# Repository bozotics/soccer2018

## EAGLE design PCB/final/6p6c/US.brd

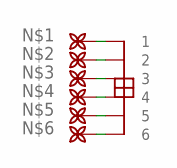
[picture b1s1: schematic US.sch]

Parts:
C1: 6P6C_FEMALESMD; 6P6C_FEMALE
PAD1, PAD2, PAD3, PAD4, PAD5, PAD6: BETTERPAD_2.54; SUPERIORSIM

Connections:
unnamed: C1.1, PAD1..
unnamed: C1.2, PAD2..
unnamed: C1.3, PAD3..
unnamed: C1.4, PAD4..
unnamed: C1.5, PAD5..
unnamed: C1.6, PAD6..

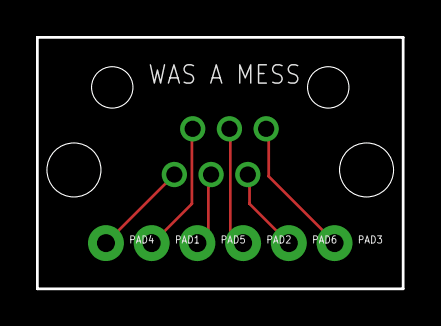
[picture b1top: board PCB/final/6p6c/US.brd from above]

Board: 2 copper layers, 20.3 x 14.0 mm, 7 parts (0 on the bottom side), 6 nets.

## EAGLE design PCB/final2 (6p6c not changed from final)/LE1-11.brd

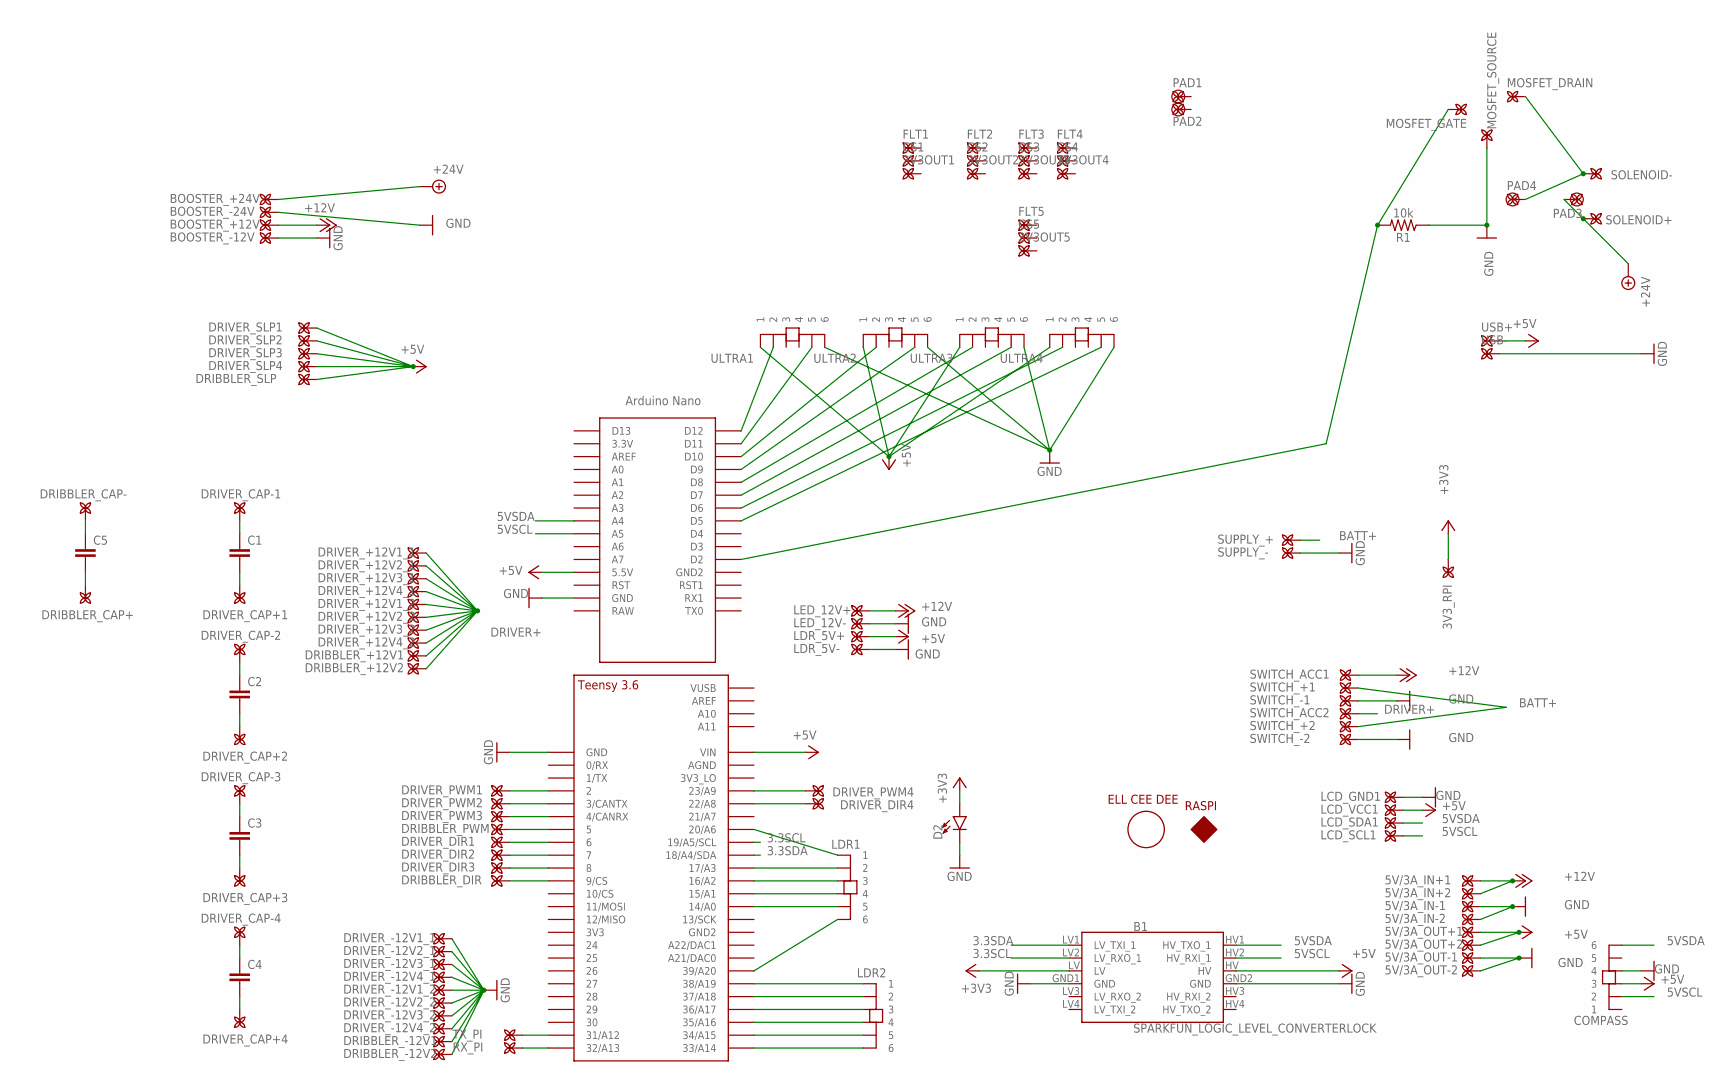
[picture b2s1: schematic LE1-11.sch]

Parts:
3V3OUT1, 3V3OUT2, 3V3OUT3, 3V3OUT4, 3V3OUT5, 3V3_RPI, 5V/3A_IN+1, 5V/3A_IN+2, 5V/3A_IN-1, 5V/3A_IN-2, 5V/3A_OUT+1, 5V/3A_OUT+2, 5V/3A_OUT-1, 5V/3A_OUT-2: BETTERPAD_2.54; SUPERIORSIM
B1: SPARKFUN_LOGIC_LEVEL_CONVERTERLOCK; SPARKFUN_LOGIC_LEVEL_CONVERTER_LOCK
BOOSTER_+12V, BOOSTER_+24V: BETTERPAD_2.54; SUPERIORSIM
BOOSTER_-12V, BOOSTER_-24V: BETTERPAD_2.54; SUPERIORSIM
C1, C2, C3, C4, C5: C5/7.2; C5B7.2
COMPASS: 6P6C_FEMALESMD; 6P6C_FEMALE
CS1, CS2, CS3, CS4, CS5: BETTERPAD_2.54; SUPERIORSIM
D2: LED-3MM-NO_SILK; LED_3MM-NS
DRIBBLER_+12V1, DRIBBLER_+12V2: BETTERPAD_2.54; SUPERIORSIM
DRIBBLER_-12V1, DRIBBLER_-12V2: BETTERPAD_2.54; SUPERIORSIM
DRIBBLER_CAP+: BETTERPAD_2.54; SUPERIORSIM
DRIBBLER_CAP-: BETTERPAD_2.54; SUPERIORSIM
DRIBBLER_DIR: BETTERPAD_2.54; SUPERIORSIM
DRIBBLER_PWM: BETTERPAD_2.54; SUPERIORSIM
DRIBBLER_SLP: BETTERPAD_2.54; SUPERIORSIM
DRIVER_+12V1_1, DRIVER_+12V1_2, DRIVER_+12V2_1, DRIVER_+12V2_2, DRIVER_+12V3_1, DRIVER_+12V3_2, DRIVER_+12V4_1, DRIVER_+12V4_2: BETTERPAD_2.54; SUPERIORSIM
DRIVER_-12V1_1, DRIVER_-12V1_2, DRIVER_-12V2_1, DRIVER_-12V2_2, DRIVER_-12V3_1, DRIVER_-12V3_2, DRIVER_-12V4_1, DRIVER_-12V4_2: BETTERPAD_2.54; SUPERIORSIM
DRIVER_CAP+1, DRIVER_CAP+2, DRIVER_CAP+3, DRIVER_CAP+4: BETTERPAD_2.54; SUPERIORSIM
DRIVER_CAP-1, DRIVER_CAP-2, DRIVER_CAP-3, DRIVER_CAP-4: BETTERPAD_2.54; SUPERIORSIM
DRIVER_DIR1, DRIVER_DIR2, DRIVER_DIR3, DRIVER_DIR4: BETTERPAD_2.54; SUPERIORSIM
DRIVER_PWM1, DRIVER_PWM2, DRIVER_PWM3, DRIVER_PWM4: BETTERPAD_2.54; SUPERIORSIM
DRIVER_SLP1, DRIVER_SLP2, DRIVER_SLP3, DRIVER_SLP4: BETTERPAD_2.54; SUPERIORSIM
FLT1, FLT2, FLT3, FLT4, FLT5: BETTERPAD_2.54; SUPERIORSIM
LCD1: LCD-16X2SILK; LCD-16X2
LCD_GND1: BETTERPAD_2.54; SUPERIORSIM
LCD_SCL1: BETTERPAD_2.54; SUPERIORSIM
LCD_SDA1: BETTERPAD_2.54; SUPERIORSIM
LCD_VCC1: BETTERPAD_2.54; SUPERIORSIM
LDR1, LDR2: 6P6C_FEMALESMD; 6P6C_FEMALE
LDR_5V+, LDR_5V-: BETTERPAD_2.54; SUPERIORSIM
LED_12V+, LED_12V-: BETTERPAD_2.54; SUPERIORSIM
MOSFET_DRAIN: BETTERPAD_2.54; SUPERIORSIM
MOSFET_GATE: BETTERPAD_2.54; SUPERIORSIM
MOSFET_SOURCE: BETTERPAD_2.54; SUPERIORSIM
PAD1, PAD2, PAD3, PAD4: BETTERPAD_2.54/1.5; 1,5
PCB1: RPI3
R1: 10k; AXIAL-0.3
RX_PI: BETTERPAD_2.54; SUPERIORSIM
SOLENOID+: BETTERPAD_2.54; SUPERIORSIM
SOLENOID-: BETTERPAD_2.54; SUPERIORSIM
SUPPLY_+: BETTERPAD_2.54; SUPERIORSIM
SUPPLY_-: BETTERPAD_2.54; SUPERIORSIM
SWITCH_+1, SWITCH_+2: BETTERPAD_2.54; SUPERIORSIM
SWITCH_-1, SWITCH_-2: BETTERPAD_2.54; SUPERIORSIM
SWITCH_ACC1, SWITCH_ACC2: BETTERPAD_2.54; SUPERIORSIM
TX_PI: BETTERPAD_2.54; SUPERIORSIM
U$1: TEENSY_3.5/3.6_BASIC
U$2: NANO
ULTRA1, ULTRA2, ULTRA3, ULTRA4: 6P6C_FEMALESMD; 6P6C_FEMALE
USB+: BETTERPAD_2.54; SUPERIORSIM
USB-: BETTERPAD_2.54; SUPERIORSIM

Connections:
3.3SCL: B1.LV2 (LV_RXO_1), U$1.19/A5/SCL
3.3SDA: B1.LV1 (LV_TXI_1), U$1.18/A4/SDA
5VSCL: B1.HV2 (HV_RXI_1), COMPASS.2, LCD_SCL1.., U$2.A5
5VSDA: B1.HV1 (HV_TXO_1), COMPASS.6, LCD_SDA1.., U$2.A4
+3V3: 3V3_RPI.., B1.LV, D2.A
+5V: 5V/3A_OUT+1.., 5V/3A_OUT+2.., B1.HV, COMPASS.3, DRIBBLER_SLP.., DRIVER_SLP1.., DRIVER_SLP2.., DRIVER_SLP3.., DRIVER_SLP4.., LCD_VCC1.., LDR_5V+.., U$1.VIN, U$2.5V (5.5V), ULTRA1.1, ULTRA2.1, ULTRA3.1, ULTRA4.1, USB+..
+12V: 5V/3A_IN+1.., 5V/3A_IN+2.., BOOSTER_+12V.., LED_12V+.., SWITCH_ACC1..
+24V: BOOSTER_+24V.., PAD3.P$1, SOLENOID+..
BATT+: SUPPLY_+.., SWITCH_+1.., SWITCH_+2..
DRIVER+: DRIBBLER_+12V1.., DRIBBLER_+12V2.., DRIVER_+12V1_1.., DRIVER_+12V1_2.., DRIVER_+12V2_1.., DRIVER_+12V2_2.., DRIVER_+12V3_1.., DRIVER_+12V3_2.., DRIVER_+12V4_1.., DRIVER_+12V4_2.., SWITCH_ACC2..
GND: 5V/3A_IN-1.., 5V/3A_IN-2.., 5V/3A_OUT-1.., 5V/3A_OUT-2.., B1.GND1 (GND), B1.GND2 (GND), BOOSTER_-12V.., BOOSTER_-24V.., COMPASS.4, D2.K (C), DRIBBLER_-12V1.., DRIBBLER_-12V2.., DRIVER_-12V1_1.., DRIVER_-12V1_2.., DRIVER_-12V2_1.., DRIVER_-12V2_2.., DRIVER_-12V3_1.., DRIVER_-12V3_2.., DRIVER_-12V4_1.., DRIVER_-12V4_2.., LCD_GND1.., LDR_5V-.., LED_12V-.., MOSFET_SOURCE.., R1.P$1 (1), SUPPLY_-.., SWITCH_-1.., SWITCH_-2.., U$1.GND, U$2.GND, ULTRA1.6, ULTRA2.6, ULTRA3.6, ULTRA4.6, USB-..
unnamed: LDR1.6, U$1.39/A20
unnamed: TX_PI.., U$1.31/A12
unnamed: RX_PI.., U$1.32/A13
unnamed: DRIBBLER_DIR.., U$1.9/CS
unnamed: DRIVER_DIR3.., U$1.8
unnamed: LDR1.5, U$1.14/A0
unnamed: LDR1.4, U$1.15/A1
unnamed: LDR1.3, U$1.16/A2
unnamed: LDR1.2, U$1.17/A3
unnamed: LDR1.1, U$1.20/A6
unnamed: DRIVER_DIR2.., U$1.7
unnamed: MOSFET_DRAIN.., PAD4.P$1, SOLENOID-..
unnamed: DRIVER_PWM4.., U$1.23/A9
unnamed: DRIVER_DIR4.., U$1.22/A8
unnamed: C4.2, DRIVER_CAP+4..
unnamed: DRIVER_DIR1.., U$1.6
unnamed: LDR2.1, U$1.38/A19
unnamed: LDR2.2, U$1.37/A18
unnamed: LDR2.3, U$1.36/A17
unnamed: LDR2.4, U$1.35/A16
unnamed: LDR2.5, U$1.34/A15
unnamed: LDR2.6, U$1.33/A14
unnamed: DRIBBLER_PWM.., U$1.5
unnamed: DRIVER_PWM3.., U$1.4/CANRX
unnamed: U$2.D12, ULTRA1.2
unnamed: C4.1, DRIVER_CAP-4..
unnamed: U$2.D11, ULTRA1.5
unnamed: U$2.D10, ULTRA2.2
unnamed: U$2.D9, ULTRA2.5
unnamed: C3.2, DRIVER_CAP+3..
unnamed: C3.1, DRIVER_CAP-3..
unnamed: C2.2, DRIVER_CAP+2..
unnamed: C2.1, DRIVER_CAP-2..
unnamed: C1.2, DRIVER_CAP+1..
unnamed: C1.1, DRIVER_CAP-1..
unnamed: C5.1, DRIBBLER_CAP-..
unnamed: C5.2, DRIBBLER_CAP+..
unnamed: U$2.D8, ULTRA3.2
unnamed: U$2.D7, ULTRA3.5
unnamed: U$2.D6, ULTRA4.2
unnamed: U$2.D5, ULTRA4.5
unnamed: DRIVER_PWM2.., U$1.3/CANTX
unnamed: DRIVER_PWM1.., U$1.2
unnamed: MOSFET_GATE.., R1.P$2 (2), U$2.D2

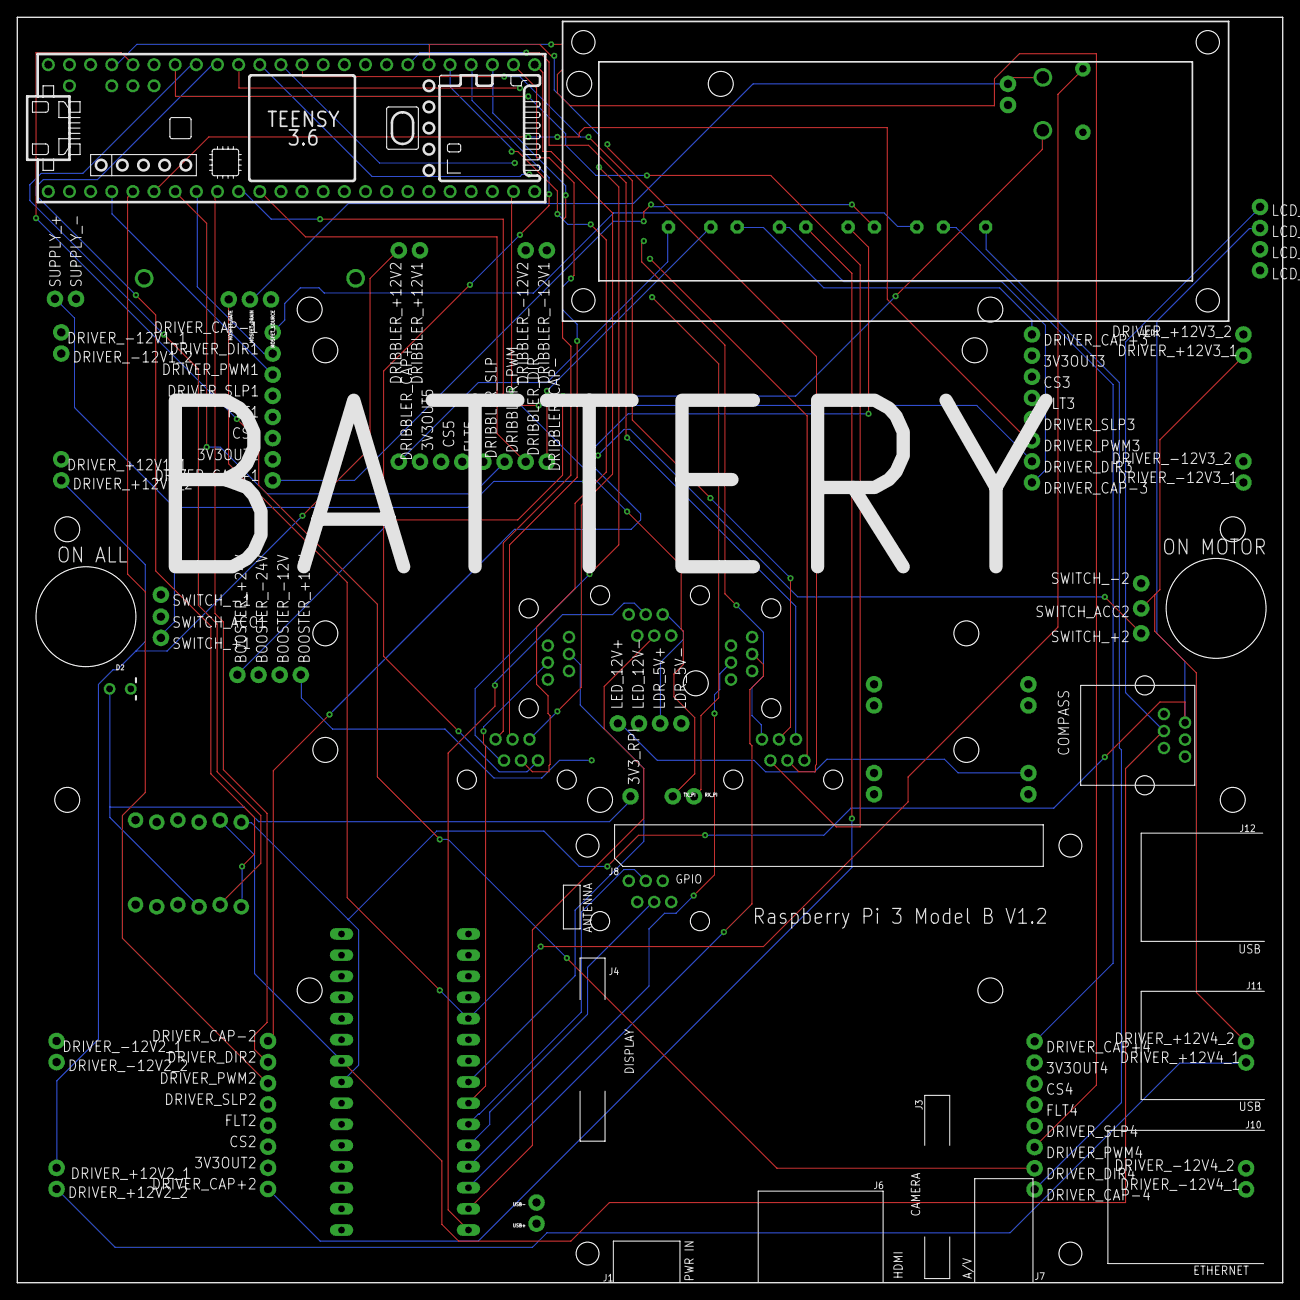
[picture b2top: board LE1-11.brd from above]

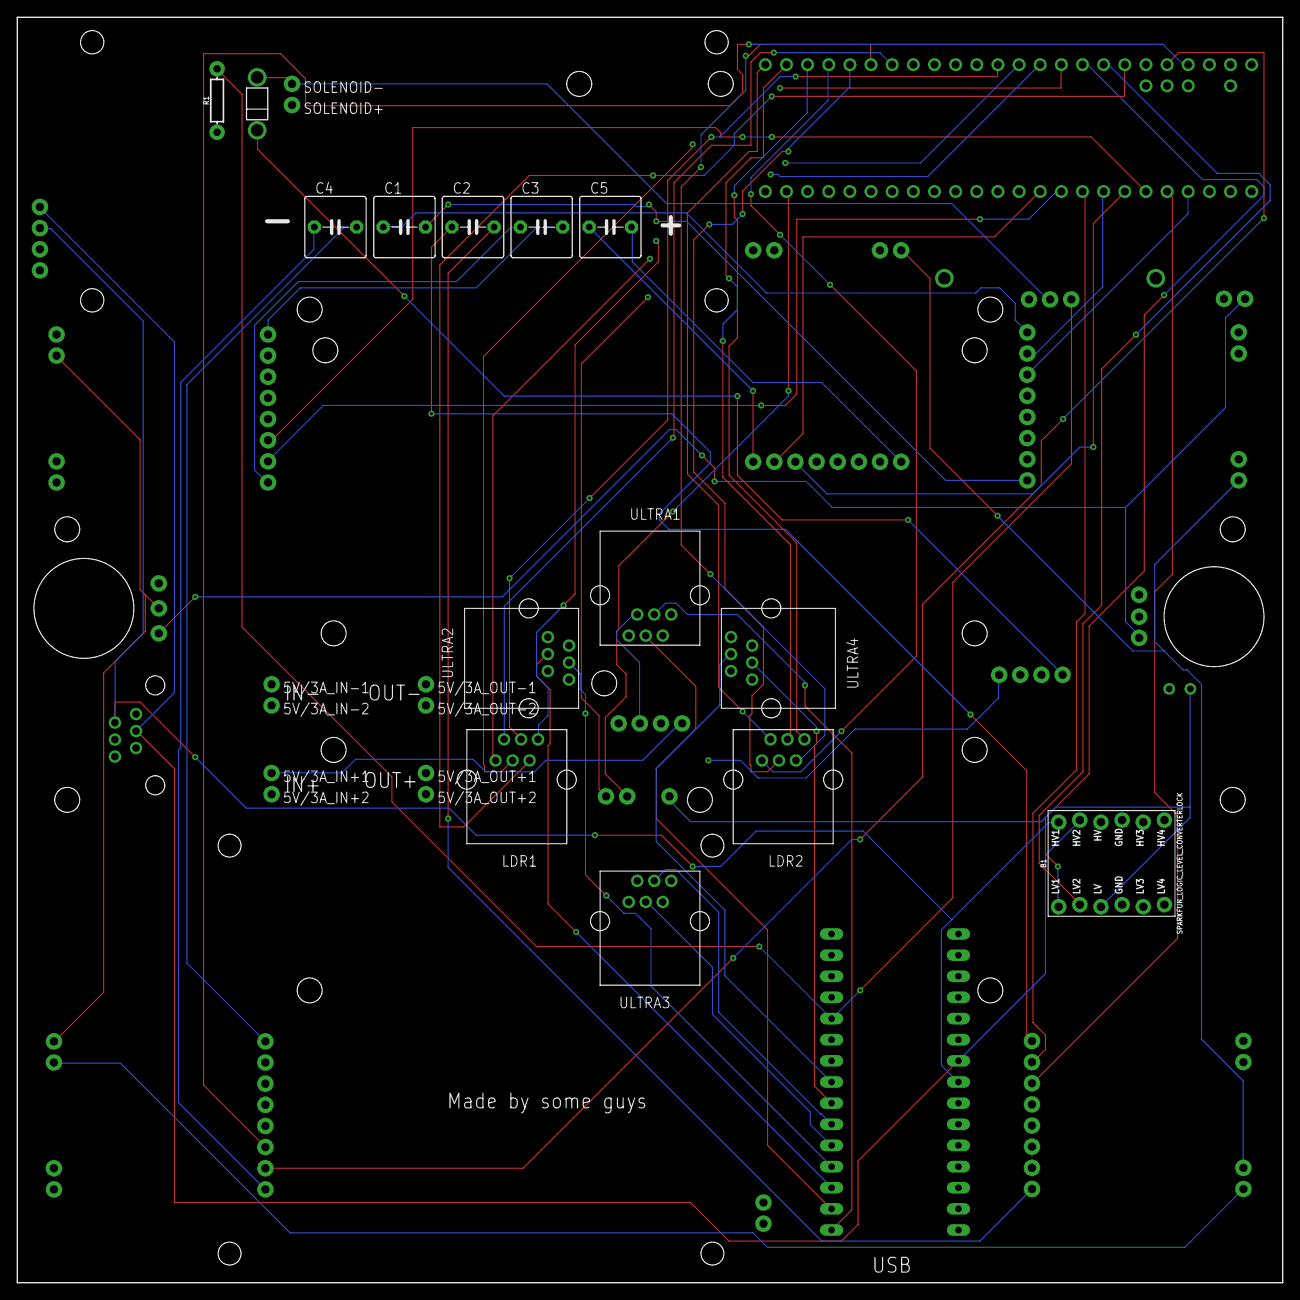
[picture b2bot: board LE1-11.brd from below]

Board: 4 copper layers, 152.0 x 152.0 mm, 121 parts (24 on the bottom side), 55 nets.

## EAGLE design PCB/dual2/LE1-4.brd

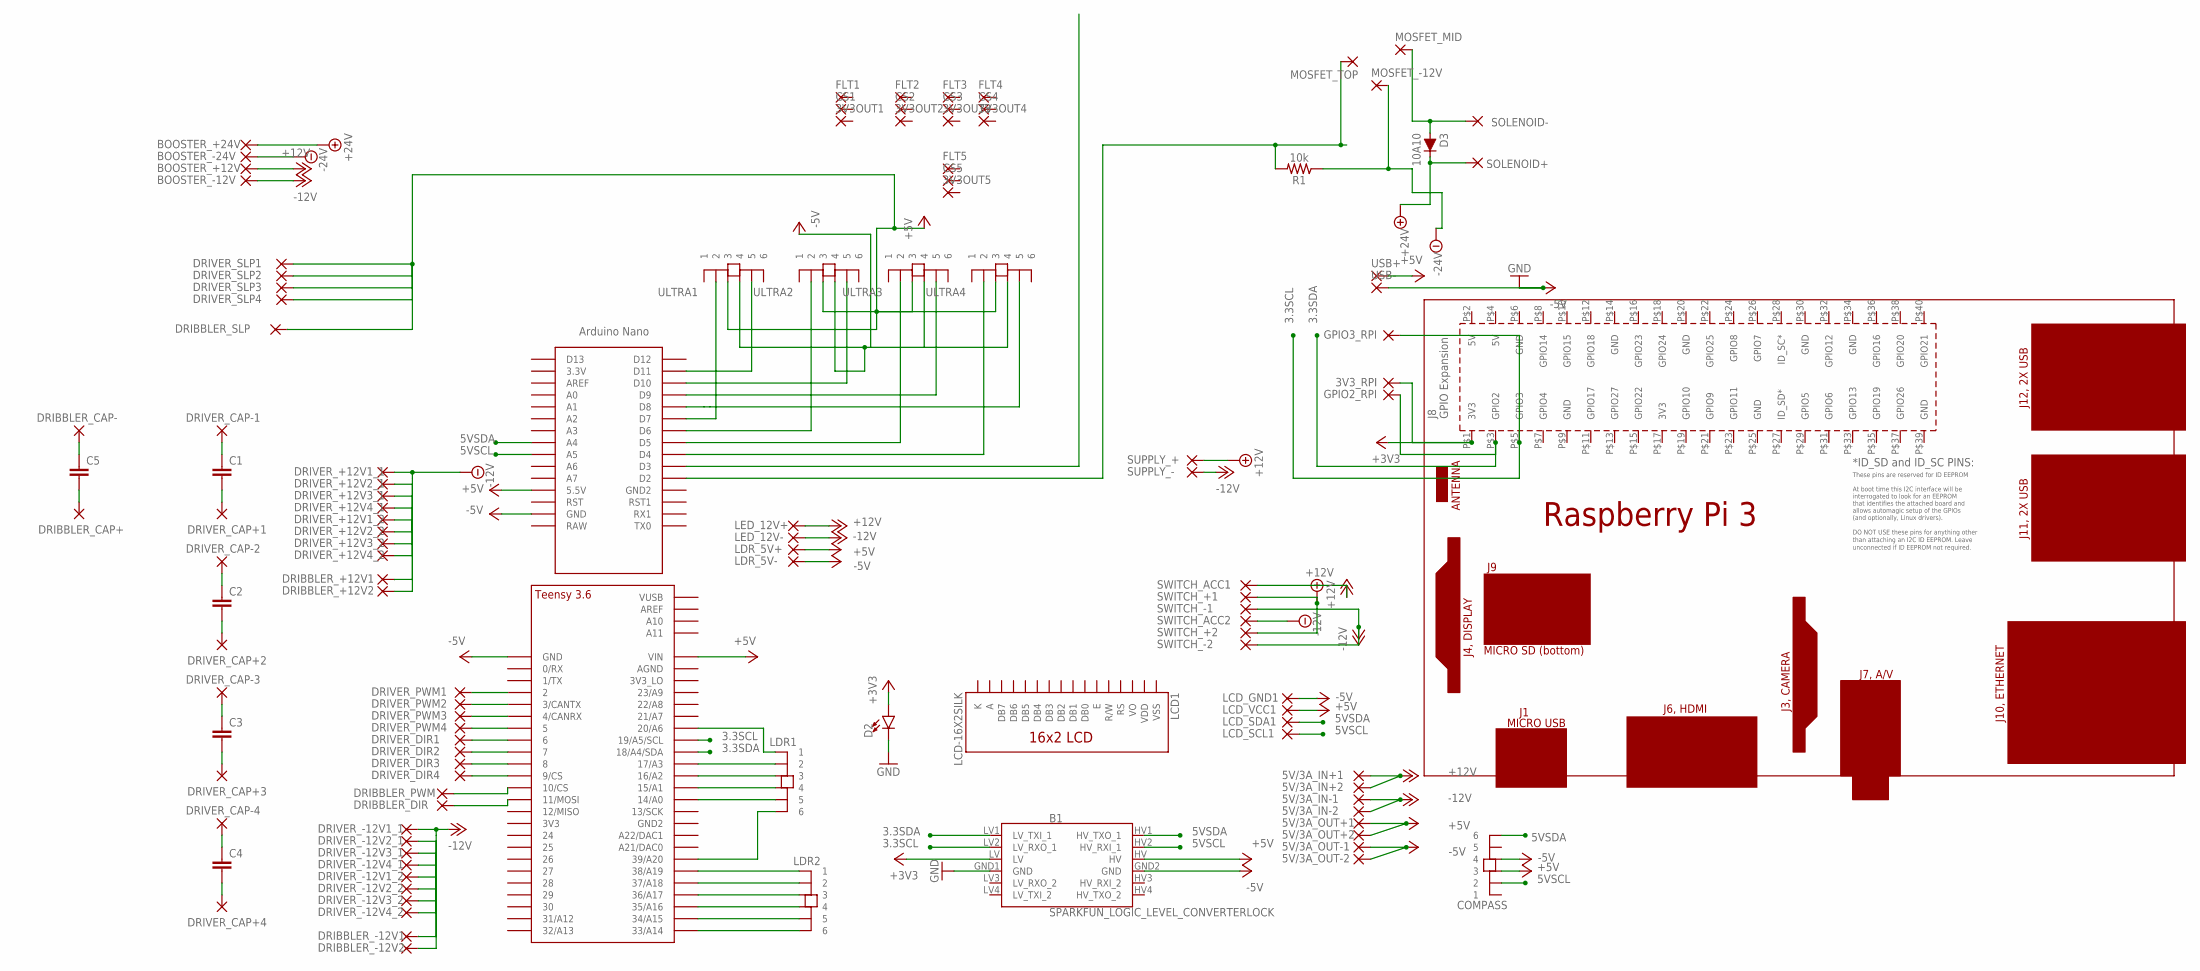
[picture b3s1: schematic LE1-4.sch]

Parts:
3V3OUT1, 3V3OUT2, 3V3OUT3, 3V3OUT4, 3V3OUT5, 3V3_RPI: 2,54/1,0
5V/3A_IN+1, 5V/3A_IN+2, 5V/3A_IN-1, 5V/3A_IN-2, 5V/3A_OUT+1, 5V/3A_OUT+2, 5V/3A_OUT-1, 5V/3A_OUT-2: WIREPAD2,54/1,0; 2,54/1,0
B1: SPARKFUN_LOGIC_LEVEL_CONVERTERLOCK; SPARKFUN_LOGIC_LEVEL_CONVERTER_LOCK
BOOSTER_+12V, BOOSTER_+24V: WIREPAD2,54/1,0; 2,54/1,0
BOOSTER_-12V, BOOSTER_-24V: WIREPAD2,54/1,0; 2,54/1,0
C1, C2, C3, C4, C5: C5/7.2; C5B7.2
COMPASS: 6P6C_FEMALESMD; 6P6C_FEMALE
CS1, CS2, CS3, CS4, CS5: 2,54/1,0
D2: LED-3MM-NO_SILK; LED_3MM-NS
D3: 10A10; DIODE-1N4148
DRIBBLER_+12V1, DRIBBLER_+12V2: WIREPAD2,54/1,0; 2,54/1,0
DRIBBLER_-12V1, DRIBBLER_-12V2: WIREPAD2,54/1,0; 2,54/1,0
DRIBBLER_CAP+: 2,54/1,0
DRIBBLER_CAP-: 2,54/1,0
DRIBBLER_DIR: WIREPAD2,54/1,0; 2,54/1,0
DRIBBLER_PWM: WIREPAD2,54/1,0; 2,54/1,0
DRIBBLER_SLP: WIREPAD2,54/1,0; 2,54/1,0
DRIVER_+12V1_1, DRIVER_+12V1_2, DRIVER_+12V2_1, DRIVER_+12V2_2, DRIVER_+12V3_1, DRIVER_+12V3_2, DRIVER_+12V4_1, DRIVER_+12V4_2: WIREPAD2,54/1,0; 2,54/1,0
DRIVER_-12V1_1, DRIVER_-12V1_2, DRIVER_-12V2_1, DRIVER_-12V2_2, DRIVER_-12V3_1, DRIVER_-12V3_2, DRIVER_-12V4_1, DRIVER_-12V4_2: WIREPAD2,54/1,0; 2,54/1,0
DRIVER_CAP+1, DRIVER_CAP+2, DRIVER_CAP+3, DRIVER_CAP+4: 2,54/1,0
DRIVER_CAP-1, DRIVER_CAP-2, DRIVER_CAP-3, DRIVER_CAP-4: 2,54/1,0
DRIVER_DIR1, DRIVER_DIR2, DRIVER_DIR3, DRIVER_DIR4: WIREPAD2,54/1,0; 2,54/1,0
DRIVER_PWM1, DRIVER_PWM2, DRIVER_PWM3, DRIVER_PWM4: WIREPAD2,54/1,0; 2,54/1,0
DRIVER_SLP1, DRIVER_SLP2, DRIVER_SLP3, DRIVER_SLP4: WIREPAD2,54/1,0; 2,54/1,0
FLT1, FLT2, FLT3, FLT4, FLT5: 2,54/1,0
GPIO2_RPI, GPIO3_RPI: 2,54/1,0
LCD1: LCD-16X2SILK; LCD-16X2
LCD_GND1: WIREPAD2,54/1,0; 2,54/1,0
LCD_SCL1: WIREPAD2,54/1,0; 2,54/1,0
LCD_SDA1: WIREPAD2,54/1,0; 2,54/1,0
LCD_VCC1: WIREPAD2,54/1,0; 2,54/1,0
LDR1, LDR2: 6P6C_FEMALESMD; 6P6C_FEMALE
LDR_5V+, LDR_5V-: 2,54/1,0
LED_12V+, LED_12V-: 2,54/1,0
MOSFET_-12V: 2,54/1,0
MOSFET_MID: 2,54/1,0
MOSFET_TOP: 2,54/1,0
PCB1: RPI3
R1: 10k; AXIAL-0.3
SOLENOID+: 2,54/1,0
SOLENOID-: 2,54/1,0
SUPPLY_+: WIREPAD2,54/1,0; 2,54/1,0
SUPPLY_-: WIREPAD2,54/1,0; 2,54/1,0
SWITCH_+1, SWITCH_+2: WIREPAD2,54/1,0; 2,54/1,0
SWITCH_-1, SWITCH_-2: WIREPAD2,54/1,0; 2,54/1,0
SWITCH_ACC1, SWITCH_ACC2: WIREPAD2,54/1,0; 2,54/1,0
U$1: TEENSY_3.5/3.6_BASIC
U$2: NANO
ULTRA1, ULTRA2, ULTRA3, ULTRA4: 6P6C_FEMALESMD; 6P6C_FEMALE
USB+: 2,54/1,0
USB-: 2,54/1,0

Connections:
3.3SCL: B1.LV2 (LV_RXO_1), GPIO3_RPI.1, PCB1.P$5 (GPIO3), U$1.19/A5/SCL
3.3SDA: B1.LV1 (LV_TXI_1), GPIO2_RPI.1, PCB1.P$3 (GPIO2), U$1.18/A4/SDA
5VSCL: B1.HV2 (HV_RXI_1), LCD_SCL1.1, U$2.A5
5VSDA: B1.HV1 (HV_TXO_1), LCD_SDA1.1, U$2.A4
+3V3: 3V3_RPI.1, B1.LV, D2.A, PCB1.P$1 (3V3)
+5V: 5V/3A_OUT+1.1, 5V/3A_OUT+2.1, B1.HV, COMPASS.3, DRIBBLER_SLP.1, DRIVER_SLP1.1, DRIVER_SLP2.1, DRIVER_SLP3.1, DRIVER_SLP4.1, LCD_VCC1.1, LDR_5V+.1, U$1.VIN, U$2.5V (5.5V), ULTRA1.3, ULTRA2.3, ULTRA3.3, ULTRA4.3, USB+.1
+12V: 5V/3A_IN+1.1, 5V/3A_IN+2.1, BOOSTER_+12V.1, D3.C, LED_12V+.1, SOLENOID+.1, SUPPLY_+.1, SWITCH_+1.1, SWITCH_+2.1, SWITCH_ACC1.1
+24V: BOOSTER_+24V.1
-5V: 5V/3A_OUT-1.1, 5V/3A_OUT-2.1, B1.GND2 (GND), COMPASS.4, LCD_GND1.1, LDR_5V-.1, U$1.GND, U$2.GND, ULTRA1.4, ULTRA2.4, ULTRA3.4, ULTRA4.4
-12V: 5V/3A_IN-1.1, 5V/3A_IN-2.1, BOOSTER_-12V.1, DRIBBLER_+12V1.1, DRIBBLER_+12V2.1, DRIBBLER_-12V1.1, DRIBBLER_-12V2.1, DRIVER_+12V1_1.1, DRIVER_+12V1_2.1, DRIVER_+12V2_1.1, DRIVER_+12V2_2.1, DRIVER_+12V3_1.1, DRIVER_+12V3_2.1, DRIVER_+12V4_1.1, DRIVER_+12V4_2.1, DRIVER_-12V1_1.1, DRIVER_-12V1_2.1, DRIVER_-12V2_1.1, DRIVER_-12V2_2.1, DRIVER_-12V3_1.1, DRIVER_-12V3_2.1, DRIVER_-12V4_1.1, DRIVER_-12V4_2.1, LED_12V-.1, MOSFET_-12V.1, R1.P$1 (1), SUPPLY_-.1, SWITCH_-1.1, SWITCH_-2.1, SWITCH_ACC2.1
-24V: BOOSTER_-24V.1
A: LCD1.15 (A)
GND: B1.GND1 (GND), D2.K (C), USB-.1
K: LCD1.16 (K)
unnamed: LDR1.6, U$1.39/A20
unnamed: DRIBBLER_PWM.1, U$1.10/CS
unnamed: DRIBBLER_DIR.1, U$1.11/MOSI
unnamed: DRIVER_PWM1.1, U$1.2
unnamed: DRIVER_PWM2.1, U$1.3/CANTX
unnamed: LDR1.2, U$1.17/A3
unnamed: LDR1.3, U$1.16/A2
unnamed: LDR1.4, U$1.15/A1
unnamed: LDR1.5, U$1.14/A0
unnamed: LDR1.1, U$1.20/A6
unnamed: DRIVER_PWM3.1, U$1.4/CANRX
unnamed: D3.A, MOSFET_MID.1, SOLENOID-.1
unnamed: MOSFET_TOP.1, R1.P$2 (2), U$2.D2
unnamed: DRIVER_PWM4.1, U$1.5
unnamed: C5.1, DRIBBLER_CAP-.1
unnamed: DRIVER_DIR1.1, U$1.6
unnamed: LDR2.1, U$1.38/A19
unnamed: LDR2.2, U$1.37/A18
unnamed: LDR2.3, U$1.36/A17
unnamed: LDR2.4, U$1.35/A16
unnamed: LDR2.5, U$1.34/A15
unnamed: LDR2.6, U$1.33/A14
unnamed: DRIVER_DIR2.1, U$1.7
unnamed: DRIVER_DIR3.1, U$1.8
unnamed: DRIVER_DIR4.1, U$1.9/CS
unnamed: C5.2, DRIBBLER_CAP+.1
unnamed: U$2.D11, ULTRA1.5
unnamed: U$2.D10, ULTRA2.5
unnamed: U$2.D9, ULTRA3.5
unnamed: C1.1, DRIVER_CAP-1.1
unnamed: C1.2, DRIVER_CAP+1.1
unnamed: C2.1, DRIVER_CAP-2.1
unnamed: C2.2, DRIVER_CAP+2.1
unnamed: C3.1, DRIVER_CAP-3.1
unnamed: C3.2, DRIVER_CAP+3.1
unnamed: C4.1, DRIVER_CAP-4.1
unnamed: C4.2, DRIVER_CAP+4.1
unnamed: U$2.D8, ULTRA4.5
unnamed: U$2.D7, ULTRA1.2
unnamed: U$2.D6, ULTRA2.2
unnamed: U$2.D5, ULTRA3.2
unnamed: U$2.D4, ULTRA4.2
VDD: LCD1.2 (VDD)
VSS: LCD1.1 (VSS)

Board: 2 copper layers, 118 parts (17 on the bottom side), 52 nets, no tracks yet.

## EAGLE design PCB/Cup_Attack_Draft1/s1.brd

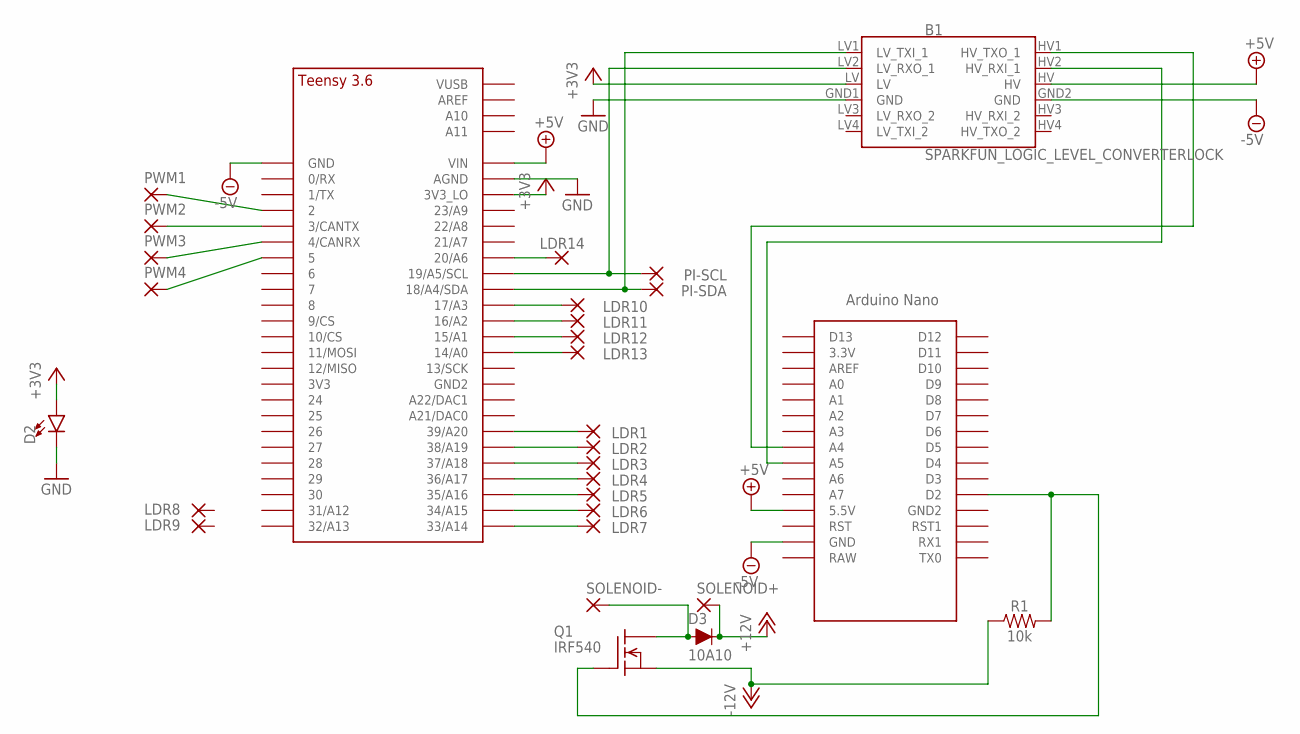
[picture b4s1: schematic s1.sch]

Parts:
B1: SPARKFUN_LOGIC_LEVEL_CONVERTERLOCK; SPARKFUN_LOGIC_LEVEL_CONVERTER_LOCK
D2: LED-3MM-NO_SILK; LED_3MM-NS
D3: 10A10; DIODE-1N4148
LDR1, LDR2, LDR3, LDR4, LDR5, LDR6, LDR7, LDR8, LDR9, LDR10, LDR11, LDR12, LDR13, LDR14: 2,54/1,0
PI-SCL: 2,54/1,0
PI-SDA: 2,54/1,0
PWM1, PWM2, PWM3, PWM4: 2,54/1,0
Q1: IRF540; TO220
R1: 10k; AXIAL-0.3
SOLENOID+: 2,54/1,0
SOLENOID-: 2,54/1,0
U$1: TEENSY_3.5/3.6_BASIC
U$2: NANO

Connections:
+3V3: B1.LV, D2.A, U$1.3V3_LO
+5V: B1.HV, U$1.VIN, U$2.5V (5.5V)
+12V: D3.C, SOLENOID+.1
-5V: B1.GND2 (GND), U$1.GND, U$2.GND
-12V: Q1.3 (S), R1.P$1 (1)
GND: B1.GND1 (GND), D2.K (C), U$1.AGND
unnamed: B1.HV1 (HV_TXO_1), U$2.A4
unnamed: B1.HV2 (HV_RXI_1), U$2.A5
unnamed: Q1.1 (G), R1.P$2 (2), U$2.D2
unnamed: D3.A, Q1.2 (D), SOLENOID-.1
unnamed: B1.LV2 (LV_RXO_1), PI-SCL.1, U$1.19/A5/SCL
unnamed: B1.LV1 (LV_TXI_1), PI-SDA.1, U$1.18/A4/SDA
unnamed: PWM4.1, U$1.5
unnamed: PWM3.1, U$1.4/CANRX
unnamed: PWM2.1, U$1.3/CANTX
unnamed: PWM1.1, U$1.2
unnamed: LDR14.1, U$1.20/A6
unnamed: LDR10.1, U$1.17/A3
unnamed: LDR11.1, U$1.16/A2
unnamed: LDR12.1, U$1.15/A1
unnamed: LDR13.1, U$1.14/A0
unnamed: LDR1.1, U$1.39/A20
unnamed: LDR2.1, U$1.38/A19
unnamed: LDR3.1, U$1.37/A18
unnamed: LDR4.1, U$1.36/A17
unnamed: LDR5.1, U$1.35/A16
unnamed: LDR6.1, U$1.34/A15
unnamed: LDR7.1, U$1.33/A14

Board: 2 copper layers, 29 parts (0 on the bottom side), 28 nets, no tracks yet.

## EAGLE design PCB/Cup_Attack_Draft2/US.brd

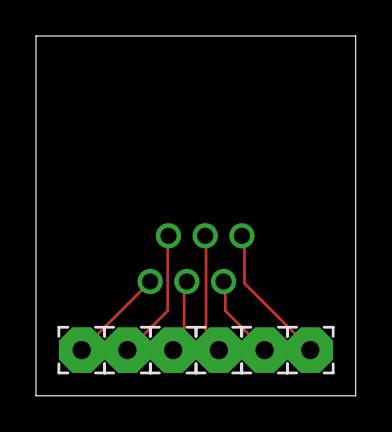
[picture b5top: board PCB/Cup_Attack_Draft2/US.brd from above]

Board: 2 copper layers, 17.8 x 20.0 mm, 7 parts (0 on the bottom side), 6 nets.

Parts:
C1: 6P6C_FEMALE
PAD1, PAD2, PAD3, PAD4, PAD5, PAD6: 2,54/1,0

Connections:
unnamed: C1.1, PAD1.1
unnamed: C1.2, PAD2.1
unnamed: C1.3, PAD3.1
unnamed: C1.4, PAD4.1
unnamed: C1.5, PAD5.1
unnamed: C1.6, PAD6.1

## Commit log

2018-10-28 upload old code

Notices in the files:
parts and their libraries:
SparkFun-Boards: Licensing: Creative Commons ShareAlike 4.0 International - https://creativecommons.org/licenses/by-sa/4.0
